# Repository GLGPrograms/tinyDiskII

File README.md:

# tinyDiskII

Homemade floppy disk emulator for Apple II series computers

> :hammer: Developement branch

> :warning: **Work in progress**: read carefully the README before trying to reproduce this project!

tinyDiskII is able to simulate an [Apple Disk II](https://it.wikipedia.org/wiki/Disk_II) both in reading and writing.
Disk images are stored into a FAT16 formatted SD Card.
Each disk image must be a DOS 3.3 floppy image, saved as .NIC.
A cross platform .NIC <-> .DSK conversion tool will be available soon on this repository.
Floppy formatting is currently not supported, but it is currently under developement.

## BOM

| Reference(s)                                  |        Description        |         Notes          |
| :-------------------------------------------- | :-----------------------: | :--------------------: |
| C1, C2, C3, C4, C5, C6, C8, C9, C10, C11, C12 |    0805 100n Capacitor    |                        |
| D1, D2                                        |       0805 Red LED        |                        |
| J1                                            |      2x3 male jumper      |     ICSP connector     |
| J2                                            |     SMD SD Card slot      |                        |
| J3                                            | THT USB B Mini connector  |  Mount for USB debug   |
| J4                                            |    2x10 male connector    |    DiskII connector    |
| R5, R6                                        |            330            |                        |
| R2, R3, R4, R7, R8, R9, R10, R11, R12, R15    |            10k            |                        |
| R13, R14                                      |             0             | Replaced with a bridge |
| SW1                                           | RotaryEncoder with switch |                        |
| U2                                            |        SN74LVC244         |   5V tolerant buffer   |
| U3                                            |          CH340C           |  Mount for USB debug   |
| U4                                            |      ATxmega16A4U-A       |          MCU           |
| U5                                            |         74AHCT125         |     Level shifter      |
| U7                                            |      0.96" OLED I2C       |      7-pin model       |
| U10                                           |         AP1117-33         |  3v3 linear regulator  |

### Do Not Place, reserved for future implementations

| Reference(s) |        Feature         |
| :----------- | :--------------------: |
| U1           | Flash/EEPROM interface |
| C12          |           "            |
| R1           |           "            |
| C13, C14     |        USB ESD         |
| R13, R14     |           "            |
| D3, D4       |           "            |
| C7           |     USB self reset     |
| J5           |  Debugging connector   |

## Schematics and PCB

> :warning: Schematics and PCB layout can be found in `/schematics` folder. Please note that I had physically implemented only rev1.0, which requires some hardware patches. The issues were fixed in rev1.1, but I never put it into production. Build it at your own risk.

## Firmware

Firmware source code is in `/firmware` folder.
Code can be compiled on a linux/wsl machine through `make` command.
Make sure you have `make` and `avr-gcc` toolchanin installed.
Output binary will be generated as `/firmware/output/tinyDiskII.hex`.

In `/firmware/tests` there are some unit tests that can run on host system.
They can be compiled and executed with:

```bash
cd firmware/tests
cmake -B build .
cd build
cmake --build .
./tinyDiskII-tests
```

### Command line linterface

The serial interface is mainly used for application logging.
If no OLED display is detected, the serial interface is enabled for receiving commands.
If the OLED is connected, the command interpreter is disabled to avoid conflicts.

The following table resumes the available commands.

| Command | Arguments  | Description                                                                     |
| :------ | :--------- | :------------------------------------------------------------------------------ |
| `INIT`  | none       | Initialize the SD Card (1)                                                      |
| `CWD`   | `dirname`  | Change woring directory to `dirname`                                            |
| `UP`    | none       | Change working director to the parent directory                                 |
| `LST`   | none       | List files and directory in the current working directory                       |
| `SET`   | `filename` | Select `filename`, in current working directory, as currently inserted disk (2) |
| `REM`   | none       | Remove currently inserted disk                                                  |
| `FAT`   | `upto`     | Prints FAT entries of selected file up to index `upto` (debug)                  |
| `INFO`  | `t` `s`    | Prints .NIC file informations about sector `s` in track `t` (debug)             |

1. If OLED is not connected, the SD Card must be manually initialized.
2. At startup, no disk is inserted.

## Changelog

* rev1.0: first version
* rev1.1: fixes the issues present in rev1.0:

  * LV_DISK_READ connected to U4 pin 21;
  * SD_WP connected to U4 pin 22;
  * SD_DETECT connected to U4 pin 23;
  * Added 10K pull-up resistor to DISK_WRITE_EN;
  * Pin 4 and 16 of U3 are shorted together.

## Contributors and references

* The whole projects borns as a custom implementation of Koichi Nishida's SdiskII [[1]](https://tulip-house.ddo.jp/digital/SDISK2/english.html) [[2]](https://github.com/suaide/SDisk2), which I used as a starting point for firmware developement.
* Jörg Hagedorn made a replica of the tinyDiskII hardware rev1.1 and he found a bug in the SD sector's addressing, now fixed.
* Kamen Angelov made a replica of the tinyDiskII hardware rev1.1, he found a bug with SDHC card and he sent some fix proposal.

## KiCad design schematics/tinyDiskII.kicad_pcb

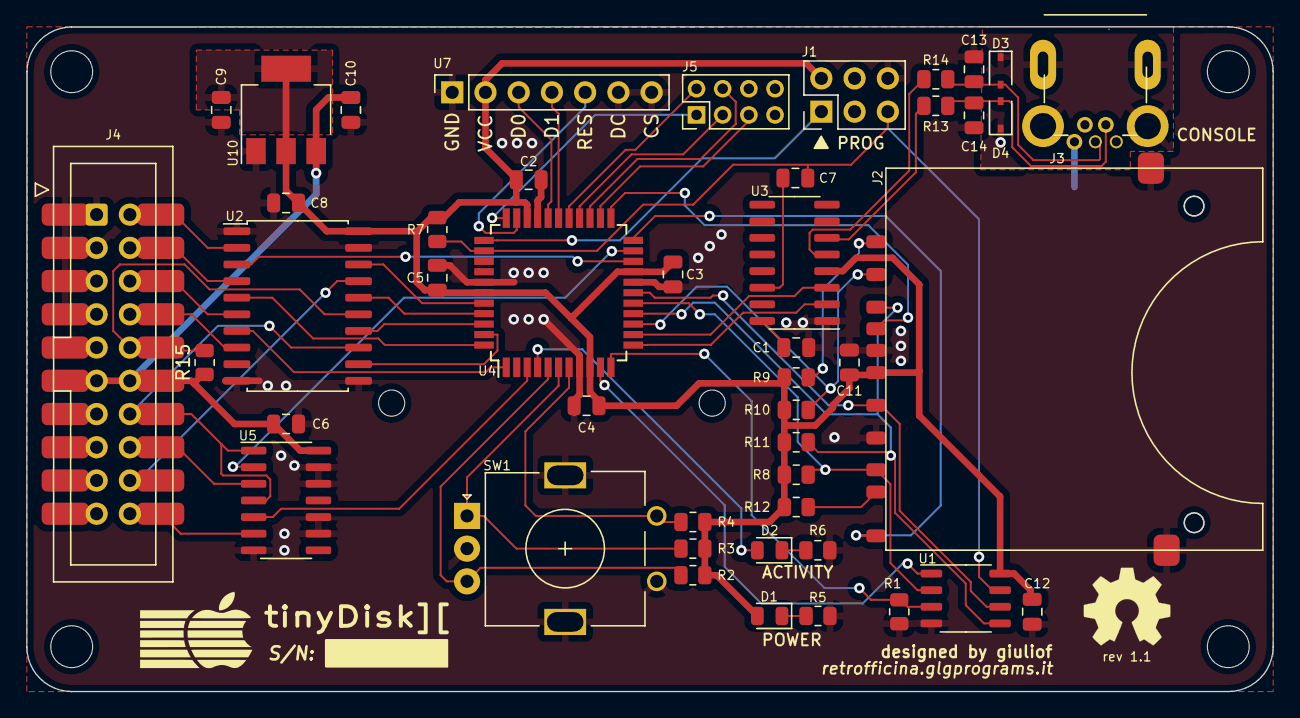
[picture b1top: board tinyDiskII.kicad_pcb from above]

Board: 2 copper layers, 95.2 x 50.8 mm, 52 parts (0 on the bottom side), 55 nets.

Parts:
C1, C3, C4, C5, C6, C8, C9, C10, C11, C12: 100n; C_0805_2012Metric
C7, C13, C14: C; C_0805_2012Metric
C?: 100n; C_0805_2012Metric
D1, D2: LED; LED_0805_2012Metric
D3, D4: -; D_SOD-323
H1, H2, H3, H4: MountingHole; MountingHole_3.2mm_M3
J2: SD_Card; SDCard
J3: USB_B_Mini; USB_Mini-B_THT_generic
J4: APPLEII_DISK_CONNECTOR; IDC-Header_2x10_P2.54mm
J5: Ext; PinHeader_2x04_P2.00mm_Vertical
J?: AVR-PDI-6; PinHeader_2x03_P2.54mm_Vertical
R1: R; R_0805_2012Metric
R2, R3, R4, R7, R8, R9, R10, R11, R12, R15: 10k; R_0805_2012Metric
R5, R6: 330; R_0805_2012Metric
R13, R14: 10; R_0805_2012Metric
SW1: RotaryEncoder_Switch
SYM1: GraphicSymbol; Apple_Logo
SYM2: Logo_Open_Hardware_Small; OSHW-Symbol_6.7x6mm_SilkScreen
U1: MX25R3235FM1xx0; SOP-8_3.9x4.9mm_P1.27mm
U2: SN74LVC244; SOIC-20W_7.5x12.8mm_P1.27mm
U3: CH340C; SOIC-16_3.9x9.9mm_P1.27mm
U5: 74AHCT125; SOIC-14_3.9x8.7mm_P1.27mm
U7: OLED_MULTI
U10: AP1117-33; SOT-223-3_TabPin2
U?: ATxmega16A4U-A; TQFP-44_10x10mm_P0.8mm

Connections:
+3V3: C1.1, C3.1, C4.1, C5.1, C8.1, C9.1, C11.1, C12.1, C?.1, D1.2 (A), J2.4 (VDD), J?.2 (VCC), R2.2, R3.2, R4.2, R7.2, R8.1, R9.1, R10.1, R11.1, R12.1, U1.8 (VCC), U2.20 (VCC), U3.4 (V3), U3.16 (VCC), U7.2 (VCC), U10.2 (VO), U?.9 (VCC), U?.19 (VCC), U?.31 (VCC), U?.39 (AVCC)
+5V: C6.1, C10.1, J4.11 (+5V), J4.12 (+5V), R15.1, U5.14 (VCC), U10.3 (VI)
/ACT_LED: D2.2 (A), U?.4 (AREFB/PB0)
/D'N: R14.1, U3.6 (UD-)
/D'P: R13.1, U3.5 (UD+)
/DAT1: J2.8 (DAT1), R12.2
/DAT2: J2.9 (DAT2), R9.2
/DISK_EN: J4.14 (EN), U2.13 (2A2), U5.1, U5.4
/DISK_READ: J4.16 (READ), U5.3
/DISK_WRITE: J4.18 (WRITE), U2.17 (2A0)
/DISK_WRITE_EN: J4.10 (WR_EN), R15.2, U2.15 (2A1)
/DN: C14.1, D4.2 (A2), J3.2 (D-), R14.2
/DP: C13.1, D3.2 (A2), J3.3 (D+), R13.2
/ENC_A: R3.1, SW1.A, U?.6 (PB2)
/ENC_B: R2.1, SW1.B, U?.5 (PB1)
/ENC_BTN: R4.1, SW1.S1, U?.7 (PB3)
/FLASH_CS: U1.1 (~CS), U?.10 (PC0)
/FLASH_WP: R1.2, U1.3 (~WP/SIO2), U?.11 (PC1)
/LV_DISK_EN: U2.7 (2Y2), U?.1 (PA5)
/LV_DISK_READ: U5.2, U?.21 (PD1)
/LV_DISK_WRITE: U2.3 (2Y0), U?.20 (PD0)
/LV_DISK_WRITE_EN: U2.5 (2Y1), U?.44 (PA4)
/LV_PHI0: U2.18 (1Y0), U?.40 (AREFA/PA0)
/LV_PHI1: U2.16 (1Y1), U?.41 (PA1)
/LV_PHI2: U2.14 (1Y2), U?.42 (PA2)
/LV_PHI3: U2.12 (1Y3), U?.43 (PA3)
/LV_WRITE_PROTECT: U5.5, U?.3 (PA7)
/OLED_RES: U7.5 (RES), U?.32 (PE2)
/OLED_SCL: U7.3 (D0), U?.29 (PE1)
/OLED_SDA: U7.4 (D1), U?.28 (PE0)
/PD4: J5.5, U?.24 (PD4)
/PD5: J5.4, U?.25 (PD5)
/PD6: J5.3, U?.26 (PD6)
/PD7: J5.2, U?.27 (PD7)
/PDI_CLK: C7.1, J?.5 (CLOCK), R7.1, U1.7 (~RESET/SIO3), U?.35 (~RESET/PDI_CLK)
/PDI_DATA: J?.1 (DATA), U?.34 (PDI_DATA)
/PE3: J5.1, U?.33 (PE3)
/PH0: J4.2 (PH0), U2.2 (1A0)
/PH1: J4.4 (PH1), U2.4 (1A1)
/PH2: J4.6 (PH2), U2.6 (1A2)
/PH3: J4.8 (PH3), U2.8 (1A3)
/SD_CS: J2.1 (CD/DAT3), R10.2, U?.14 (PC4)
/SD_DETECT: J2.10 (CARD_DETECT), U?.23 (PD3)
/SD_WP: J2.11 (WRITE_PROTECT), U?.22 (PD2)
/SPI_MISO: J2.7 (DAT0), R8.2, U1.2 (SO/SIO1), U?.16 (PC6)
/SPI_MOSI: J2.2 (CMD), R11.2, U1.5 (SI/SIO0), U?.15 (PC5)
/SPI_SCK: J2.5 (CLK), U1.6 (SCLK), U?.17 (PC7)
/UART_RXD: U3.2 (TXD), U?.12 (PC2)
/UART_TXD: U3.3 (RXD), U?.13 (PC3)
/USB_SHIELD: D3.1 (A1), D4.1 (A1), J3.6 (Shield)
/WRITE_PROTECT: J4.20 (PROTECT), U5.6
GND: C1.2, C3.2, C4.2, C5.2, C6.2, C8.2, C9.2, C10.2, C11.2, C12.2, C13.2, C14.2, C?.2, J2.3 (VSS), J2.6 (VSS), J2.12 (SHELL1), J2.13 (SHELL2), J3.5 (GND), J4.1 (GND), J4.3 (GND), J4.5 (GND), J4.7 (GND), J?.6 (GND), R1.1, R5.2, R6.2, SW1.C, SW1.MP (SHIELD), SW1.S2, U1.4 (GND), U2.1 (1OE), U2.10 (GND), U2.11 (2A3), U2.19 (2OE), U3.1 (GND), U5.7 (GND), U5.9, U5.10, U5.12, U5.13, U7.1 (GND), U7.6 (DC), U7.7 (CS), U10.1 (GND), U?.8 (GND), U?.18 (GND), U?.30 (GND), U?.38 (GND)
unnamed: C7.2, U3.14 (~RTS)
unnamed: D1.1 (K), R5.1
unnamed: D2.1 (K), R6.1

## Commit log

2022-10-01 [repo] Added support for git lfs, added project image
2022-10-01 [firmware] imported codebase after a bit of cleanup
2022-10-01 [schematics] added Kicad project for hw rev 1.0
2022-10-01 [repo] Updated readme
2022-10-01 [schematics] Removed some notes from schematic
2022-10-01 [schematics] Updated missing values
2022-10-01 [repo] Updated readme and fw targets
2022-11-28 Annotations for next release
2022-11-28 [schematics] integrated changes for rev2, removed some ERC warnings
2022-11-28 [schematics] Updated power symbols
2022-12-01 [schematics] Updated power symbols, part 2
2022-12-01 [schematics] Removed old tracks, rewire in progress
2022-12-04 [schematics] updated routing fixing errata of rev1.0
2022-12-07 [schematics] rev1.1 label
2022-12-07 [repo] Updated readme with changes in schematics (rev1.1)
2022-12-07 [schematics] Missing track, fixed
2022-12-08 [sdcard] Fixed typo in initialization procedure
    After acmd 41, must wait for empty R1 (0x00), not IDLE (0x01).
2022-12-08 [encoder] use in-hardware quadrature encoder system instead of software
2022-12-08 [sdcard] faster SPI
    /4 prescaler instead of /64
2022-12-19 [sdcard] first steps toward rev 2.0
    - swapped SDCARD_CLK and SDCARD_DO pins to make use of syncronous UART
    (MSPI mode).
    - Switched from SPI to UART, MSPI mode.
2022-12-21 [repo] Note in readme
2022-12-31 [dma] first working code with DMA, only read is implemented
    ALERT: AN HARDWARE CHANGE IS NEEDED, THIS CODE IS COMPATIBLE ONLY WITH
    HARDWARE REV2.0.
    - disabled writing, since is currently not implemented through DMA;
    - removed bitbanging, no more needed;
    - sdcard SPI is handled with USART in MSPI mode, this need pin swap
    between MOSI and SCK;
2023-01-25 [dma] read/write code with DMA implemented, now with formatting support
    Tested with AppleDOS INITIALIZE command and CopyII+ V5.
    - Writing buffer size increased to keep whole SD Card sector, plus CRC
    and "end of data token". Buffer is mostly initialized at startup, only
    address and data fields are changed at runtime.
    - New writing state machine, which detects the currently writing field
    and updates the writing buffer accordingly.
2023-02-08 WIP: refactoring, piu becero fix al problema del bit slip
2023-02-11 Minor, indentation
2023-02-11 [floppy] get current volume when changing sector's content
2024-07-21 [refactor] code comments cleanup
2024-07-21 [floppy] fast workaround for a bit slip issue
2024-11-11 debug: temporary disabled disk ii interface
2024-11-11 debug: added some commands to debug sd card communication
2024-11-30 [floppy] fixed error in nic sector offset value in a FAT cluster
    It was hardcoded to work with 4 fat sectors per cluster.
    Generalized for any sectors per cluster value.
2025-01-12 [sdcard] better logging of SD Card type
2025-01-12 [sdcard] fix bad addressing for SDHC cards
2025-01-12 [repo] updated readme with prompt commands description
2025-01-13 [cli] added some commands to debug sd card communication
2025-01-14 docs: added explanation of the new debug commands, cited Jörg for his contribution in this fix
2025-01-14 docs: cited Kamen for his contribution in this fix
2026-05-04 [firmware] missing include
2026-05-04 [encoder] fixed wrong encoder steps
    - Counter register is on 16bit;
    - Each encoder turn is 4 steps;
    - Delta is signed, should use signed division instead of raw shift.
2026-05-06 [gpio] added activity led
2026-05-06 [refactoring] removed useless or-ing
2026-05-06 [sdcard] presence detection when in no gui mode
